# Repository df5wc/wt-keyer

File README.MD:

# Walkie-Talkie Keyer

So, hier isser: Der Walkie-Talkie Keyer. Das Projekt, an dem ich die letzten
Wochen nebenher rumgepusselt habe. Es ist eine komplette Hardware zum Betrieb
eines Handfunkgeräts als CW Station.

## Noch nie gestellte Fragen und ein paar Antworten:

### Was macht das Gerät?

CW über FM.

### Das kann ein Piepser, den ich ans Funkgerät halte. Wieso eine extra Hardware?

Der Walkie-Talkie Keyer übernimmt die komplette Steuerung. Er schaltet beim
ersten Zeichen das Handfunkgerät auf Sendung, generiert lokal einen Mithörton
und gibt die Morsezeichen auf das Funkgerät um wenige 100ms zeitverzögert aus.
Damit hat das Funkgerät Zeit, auf Sendung zu schalten. Mit dem Walkie-Talkie
Keyer ist CW mit einer Handfunke ähnlich komfortabel wie mit einem Gerät, das
CW native unterstützt: Einfach losmorsen. Das Gerät schaltet automatisch auf
Sendung und nach dem letzten Zeichen wieder zurück.

### Wofür braucht man das?

Ich habe es primär gebaut um auf dem Congress TOTA in CW machen zu können,
weil ich dort vermutlich nur ein Handfunkgerät haben werde. Der Walkie-Talkie
Keyer funktioniert aber nicht nur im Amateurfunk, sondern kann auch einfache
PMR Funkgeräte ansteuern und eignet sich deshalb auch zur Ausbildung oder als
Spaßprojekt für Kids. Der Keyer kann im Prinzip auch "große" Funkgeräte
ansteuern, solange diese PTT gegen Masse schalten und dafür keine hohen
Ströme/Spannungen notwendig sind.

### Gab's das nicht schon mal?

Ja, das gab's schon mal. Burkhard John (DK5JG) hat 2006 eine ähnliches Projekt
vorgestellt, den "FM-Keyer". Von diesem Gerät stammen einige der Ideen.
Schaltung, Software und Board des Walkie-Talkie Keyers sind aber komplett neu
und von mir.

### Paddle oder Handtaste?

Der Keyer kann beides, mit Handtaste ist aber keine Konfiguration möglich. Da
alle Einstellungen (bis auf "Handtaste oder Paddle") ausfallsicher gespeichert
werden, sollte das aber kein großes Problem sein. Nachdem die Konfiguration
mit einem Paddle durchgeführt wurde, kann mit genau diesen Einstellungen auch
eine Handtaste verwendet werden.

### Wie wird eine Handtaste erkannt?

Für ein Paddle wird ein 3,5 mm Stereo Klinkenstecker verwendet, für eine
Handtaste derselbe Stecker in Mono. Durch den Mono Stecker wird das rechte
Paddle ("Dah") an Masse gelegt. Das erkennt der Keyer beim Start und schaltet
direkt auf Handtaste um. Alternativ kann das rechte Paddle beim Start gedrückt
werden, oder mit dem "SK" Kommando (siehe unten) von Paddle auf Handtaste
umgeschaltet werden.

Die Einstellung "Handtaste" bleibt erhalten, bis der Keyer stromlos gemacht
wird. Ein Rückschalten durch Kommando ist nicht möglich.

### Wie bediene ich den Keyer?

Der Keyer benötigt externe 5V aus einem USB Port (Handy oder Power Bank). Er
wird auf der einen Seite mit dem Handfunkgerät verbunden. Auf der anderen
Seite wird die Taste angeschlossen. Neben der Einstellung für die Lautstärke
an der Seite gibt es an der Unterseite noch zwei Potis mit denen die Pegel für
das Handfunkgerät eingestellt werden können. Sie sollten bei der ersten
Inbetriebnahme auf jeweils 1/4 im Uhrzeigersinn eingestellt und dann nach
Gehör justiert werden. Bei Verwendung eines anderen Funkgeräts oder großen
Änderungen der Tonhöhe kann eine Nachjustierung notwendig sein.

Danach kann im Prinzip schon losgemorst werden. Zur Einstellung gibt es die
Taste &lt;Cmd&gt;. Wenn sie gedrückt und gehalten wird, können dem Keyer
Kommandos in CW gegeben werden. Hier ist die Liste der Kommandos:

* D?             query the tx delay
* Dnnn           set tx delay in ms
* IA             activate iambic A
* IB             activate iambic B
* IP             activate plain iambic mode
* M?1            query cw memory 1
* M?2            query cw memory 2
* M1...          program cw memory 1
* M2...          program cw memory 2
* O?             query tx off delay in dits
* Onn            set tx off delay in dits
* SK             switch to straight key
* SWD            disable paddle swap
* SWE            enable paddle swap
* T?             query the tone frequency
* TMD            disable training mode (TX)
* TME            enable training mode (no TX)
* Tnnn           set a tone frequency
* V?             query the software version number
* W?             query the keyer speed
* Wnn            set the keyer speed in wpm

Die Kommandos werden jeweils mit einem hohen Ton quittiert, wenn sie
erfolgreich ausgeführt wurden. Bei einem Fehler (oder einem unbekannten
Kommando) erfolgt eine Fehlerquittung (niedriger Ton).

Alle Einstellungen werden ausfallsicher gespeichert und stehen deshalb nach
dem nächsten Start genau so wieder zur Verfügung.

### Wie funktioniert das mit den CW Speichern?

Der Keyer verfügt über zwei Speicherplätze für Nachrichten in Morsecode. Diese
können über die Kommandos "M1" und "M2" programmiert und mit den Tasten
&lt;1&gt; und &lt;2&gt; abgerufen werden. Während ein Speichertext ausgegeben
wird, kann mittels Druck auf einen beliebigen Knopf oder Betätigung der
Morsetaste die Ausgabe abgebrochen werden.

Für die Programmierung wird &lt;Cmd&gt; gedrückt und "M1" oder "M2" mit dem
Paddle gegeben. Dann folgt der zu speichernde Text. Eine Pause von mindestens
2 Sekunden beendet die Eingabe mit einem Quittungston.

Um Speicherplatz zu sparen, werden alle Zeiten auf volle Vielfache der für ein
"Dit" benötigten Zeit gerundet. Der benötigte Speicherplatz pro Element mit
folgender Pause (also "Dit" oder "Dah") beträgt 1 Byte. Insgesamt stehen etwa
200 Bytes pro Speicherplatz zur Verfügung. Wird die maximale Länge eines
Speichers bei der Eingabe überschritten, erfolgt eine Fehlerquittung und der
Text wird nicht gespeichert. Die Programmierung kann auch durch Loslassen der
&lt;Cmd&gt; Taste vorzeitig abgebrochen werden (z.B. bei Fehltastung). Der
bereits gespeicherte Text bleibt dann erhalten.

### Wieso erfolgt die Tonausgabe des Handfunkgeräts über den Keyer?

Das ist bei Handfunkgeräten mit Kenwood "Norm" für den Anschluß eines externen
Mikrofons leider zwingend. Bei dieser Beschaltung werden zwei Stecker
verwendet, einer für Mikrofon/PTT, der andere für den Lautsprecher. Der
Stecker für Mikrofon/PTT führt aber keine Masse! Will man also PTT gegen Masse
schalten, muss zwingend auch der Lautsprecheranschluß verwendet werden. Dadurch
wird aber der interne Lautsprecher des Geräts abgeschaltet. Folglich muss die
Ausgabe über das angeschlossene Gerät erfolgen.

Wird eine andere Anschlußbeschaltung verwendet (von mir nicht getestet), dann
kann - falls das gewünscht ist - der "Speaker" Eingang am DIN Stecker des
Keyers einfach auf Masse gelegt, und der interne Lautsprecher des Geräts
verwendet werden. Der Mithörton kommt dann aus dem Lautsprecher des Keyers,
das Empfangssignal aus dem Lautsprecher des Funkgeräts.

### Welche Funkgeräte wurden getestet?

Ich habe den Keyer mit meinem Wouxun KG-UV6D und mit zwei verschiedenen PMR
Funkgeräten getestet. Alle diese Geräte hatten die Kenwood Anschlußbelegung.
Andere Anschlüsse sollten funktionieren, wenn PTT gegen Masse geschaltet wird
und keine hohen Ströme fliessen. Wenn keine Ausgabe des Empfangssignals über
die Keyer Hardware erfolgen soll, dann ist der entsprechende Eingang des
Keyers am DIN Stecker auf Masse zu legen.

### Ich habe ein Problem, wieso kann ich kein Issue anlegen?

Das Repository auf Github dient nur der Veröffentlichung, nicht der
Entwicklung. Für die Entwicklung wird ein anderes Repository verwendet.
Deshalb können auf Github keine Issues angelegt werden. Bei Problemen bitte
ich darum, mich per Mail zu kontaktieren.

### Gibt es bekannte Probleme?

Beim Prototyp hatte ich teilweise Probleme mit Einstrahlungen durch das
Handfunkgerät. Ich empfehle, ein abgeschirmtes Kabel für die Verbindung zum
Funkgerät zu verwenden und evtl. die Ferritperlen auf dem Board gegen kleine
Induktivitäten auszutauschen und/oder an der Stelle noch mit 100pF
abzublocken. Sobald mehr Erfahrungen vorliegen werde ich ggf. entsprechende
Änderungen der Schaltung vornehmen.

Die beiden Trimmer RV1 und RV2 werden von der Unterseite des Boards aus
bedient und haben deshalb die falsche Drehrichtung: Rechtsanschlag ist
Minimum, Linksanschlag ist Maximum.

### Ich kann mir das nicht vorstellen. Wie sieht der Keyer denn aus?

Hier sind Bilder vom aufgebauten Keyer und von einem kompletten Setup:

### Wo gibt's den Keyer zu kaufen?

Gar nicht (zumindest bei mir). Von mir gibt es

  - den Schaltplan,
  - einen PCB Entwurf,
  - die Software,
  - OpenSCAD Sourcen und STL Datei für das Gehäuse,
  - und eine minimale Doku

auf GitHub. Mit dabei ist eine Teileliste mit (größtenteils und ohne Garantie)
Reichelt Bestellnummern.

Wenn genug Interesse besteht, kann ich nochmals einen Satz Platinen fertigen
lassen und - solange übrig sind - welche abgeben. Ggf. mit programmierter AVR
CPU. Ich vertreibe aber keine Fertiggeräte oder Bausätze. Falls das jemand
machen will habe ich aber nichts dagegen.

### Ok, ich will bauen! Wie lege ich los?

Hier gibt es mehr Infos zum Aufbau:

* 
* 
* 

### Was gibt es sonst zu beachten?

Die Lizenz erlaubt so ziemlich alles, bis darauf die Entwürfe als eigene
auszugeben. Für Schäden beim Nachbau übernehme ich keine Haftung.

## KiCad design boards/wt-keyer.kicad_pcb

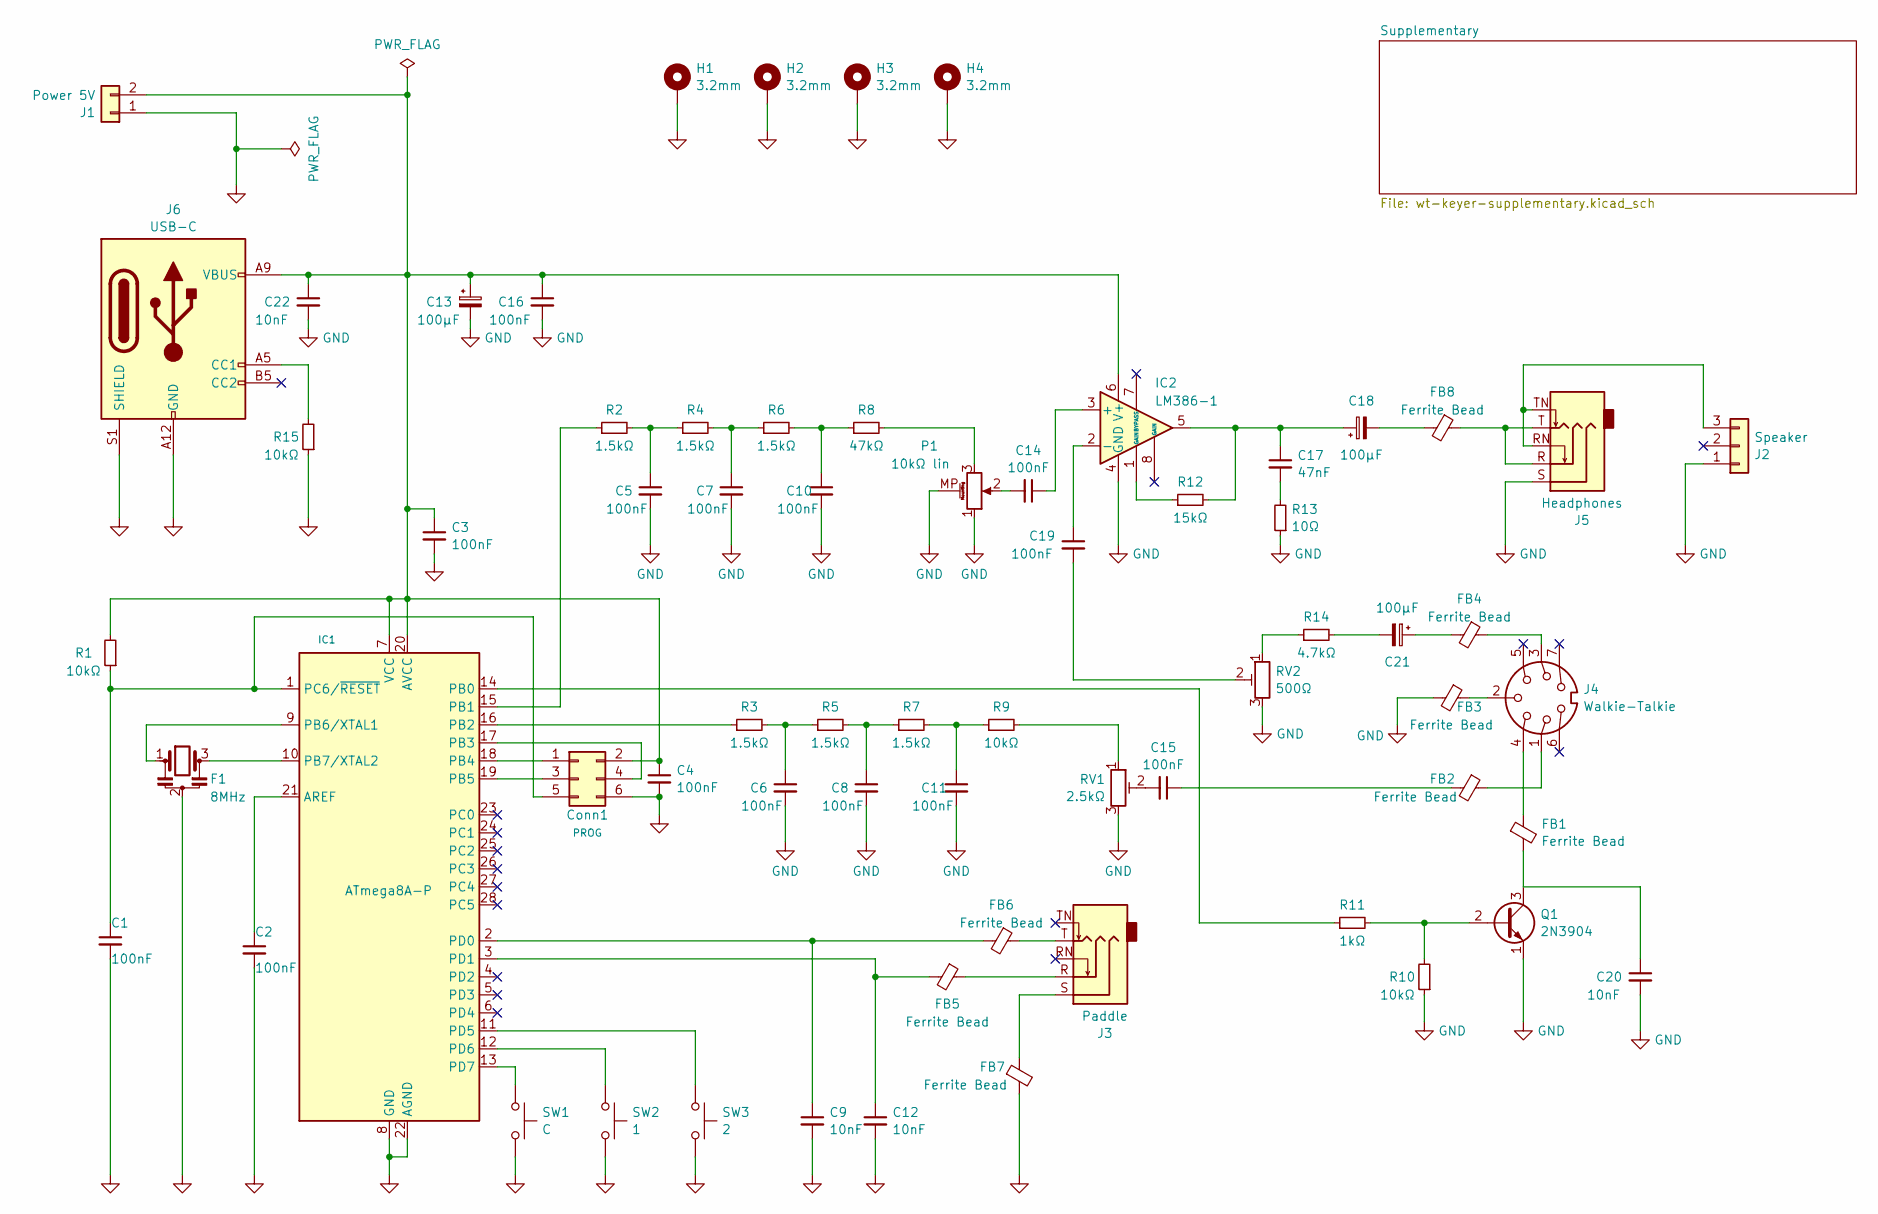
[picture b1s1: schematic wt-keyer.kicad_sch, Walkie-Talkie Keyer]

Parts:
C1, C2, C3, C4, C16: 100nF; C_Disc_D3.0mm_W1.6mm_P2.50mm
C5, C6, C7, C8, C10, C11, C14, C15, C19: 100nF; C_Rect_L4.6mm_W3.0mm_P2.50mm_MKS02_FKP02
C9, C12, C20, C22: 10nF; C_Disc_D3.0mm_W1.6mm_P2.50mm
C13, C18, C21: 100μF; CP_Radial_D5.0mm_P2.50mm
C17: 47nF; C_Rect_L4.6mm_W3.0mm_P2.50mm_MKS02_FKP02
Conn1: PROG; PinHeader_2x03_P2.54mm_Vertical
F1: 8MHz; Resonator-3Pin_W7.0mm_H2.5mm
FB1, FB2, FB3, FB4, FB5, FB6, FB7, FB8: Ferrite Bead; L_Axial_L9.5mm_D4.0mm_P2.54mm_Vertical_Fastron_SMCC
H1, H2, H3, H4: 3.2mm; MountingHole_3.2mm_M3_Pad_5.0mm_TopBottom
IC1: ATmega8A-P; DIP-28_W7.62mm
IC2: LM386-1; DIP-8_W7.62mm_Socket_LongPads
J1: Power 5V; FanPinHeader_1x02_P2.54mm_Vertical
J2: Speaker; FanPinHeader_1x03_P2.54mm_Vertical
J3: Paddle; Jack_3.5mm_Ledino_KB3SPRS_Horizontal
J4: Walkie-Talkie; DIN_7Pin_Horizontal
J5: Headphones; Jack_3.5mm_Ledino_KB3SPRS_Horizontal
J6: USB-C; USB_C_Receptacle_GCT_USB4125-xx-x-0190_6P_TopMnt_Horizontal
P1: 10kΩ lin; Potentiometer_Alps_RK09K_Single_Horizontal
Q1: 2N3904; TO-92_Inline
R1, R9, R10, R15: 10kΩ; R_Axial_DIN0207_L6.3mm_D2.5mm_P2.54mm_Vertical
R2, R3, R4, R5, R6, R7: 1.5kΩ; R_Axial_DIN0207_L6.3mm_D2.5mm_P2.54mm_Vertical
R8: 47kΩ; R_Axial_DIN0207_L6.3mm_D2.5mm_P2.54mm_Vertical
R11: 1kΩ; R_Axial_DIN0207_L6.3mm_D2.5mm_P2.54mm_Vertical
R12: 15kΩ; R_Axial_DIN0207_L6.3mm_D2.5mm_P2.54mm_Vertical
R13: 10Ω; R_Axial_DIN0207_L6.3mm_D2.5mm_P2.54mm_Vertical
R14: 4.7kΩ; R_Axial_DIN0207_L6.3mm_D2.5mm_P2.54mm_Vertical
RV1: 2.5kΩ; Potentiometer_Piher_PT-10-V10_Vertical
RV2: 500Ω; Potentiometer_Piher_PT-10-V10_Vertical
SW1: C; SW_PUSH_6mm_H4.3mm
SW2: 1; SW_PUSH_6mm_H4.3mm
SW3: 2; SW_PUSH_6mm_H4.3mm

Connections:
GND: C1.2, C2.2, C3.2, C4.2, C5.2, C6.2, C7.2, C8.2, C9.2, C10.2, C11.2, C12.2, C13.2, C16.2, C20.2, C22.2, Conn1.6, F1.2, FB3.2, FB7.2, H1.1, H2.1, H3.1, H4.1, IC1.8 (GND), IC1.22 (AGND), IC2.4 (GND), J1.1, J2.1, J5.S, J6.A12 (GND), J6.B12 (GND), J6.S1 (SHIELD), P1.1, P1.MP (MountPin), Q1.1 (E), R10.1, R13.1, R15.1, RV1.3, RV2.3, SW1.2, SW2.2, SW3.2
unnamed: C5.1, R2.2, R4.1
unnamed: C6.1, R3.2, R5.1
unnamed: C7.1, R4.2, R6.1
unnamed: C8.1, R5.2, R7.1
unnamed: C10.1, R6.2, R8.1
unnamed: C11.1, R7.2, R9.1
unnamed: C14.2, P1.2
unnamed: C15.1, FB2.2
unnamed: C15.2, RV1.2
unnamed: C17.1, C18.1, IC2.5, R12.2
unnamed: C17.2, R13.2
unnamed: C18.2, FB8.2
unnamed: C19.2, RV2.2
unnamed: C21.1, FB4.2
unnamed: C21.2, R14.2
unnamed: Conn1.1, IC1.18 (PB4)
unnamed: C3.1, C4.1, C13.1, C16.1, C22.1, Conn1.2, IC1.7 (VCC), IC1.20 (AVCC), IC2.6 (V+), J1.2, J6.A9 (VBUS), J6.B9 (VBUS), R1.2
unnamed: Conn1.3, IC1.19 (PB5)
unnamed: Conn1.4, IC1.17 (PB3)
unnamed: C1.1, Conn1.5, IC1.1 (PC6/~RESET), R1.1
unnamed: FB1.1, J4.4
unnamed: FB2.1, J4.1
unnamed: FB3.1, J4.2
unnamed: FB4.1, J4.3
unnamed: FB5.1, J3.R
unnamed: FB6.1, J3.T
unnamed: FB7.1, J3.S
unnamed: FB8.1, J5.R, J5.T
unnamed: C2.1, IC1.21 (AREF)
unnamed: IC1.14 (PB0), R11.1
unnamed: IC1.15 (PB1), R2.1
unnamed: IC1.16 (PB2), R3.1
unnamed: F1.1, IC1.9 (PB6/XTAL1)
unnamed: F1.3, IC1.10 (PB7/XTAL2)
unnamed: C9.1, FB6.2, IC1.2 (PD0)
unnamed: C12.1, FB5.2, IC1.3 (PD1)
unnamed: IC1.11 (PD5), SW3.1
unnamed: IC1.12 (PD6), SW2.1
unnamed: IC1.13 (PD7), SW1.1
unnamed: C14.1, IC2.3 (+)
unnamed: C19.1, IC2.2 (-)
unnamed: IC2.1 (GAIN), R12.1
unnamed: J2.3, J5.RN, J5.TN
unnamed: J6.A5 (CC1), R15.2
unnamed: P1.3, R8.2
unnamed: Q1.2 (B), R10.2, R11.2
unnamed: C20.1, FB1.2, Q1.3 (C)
unnamed: R9.2, RV1.1
unnamed: R14.1, RV2.1

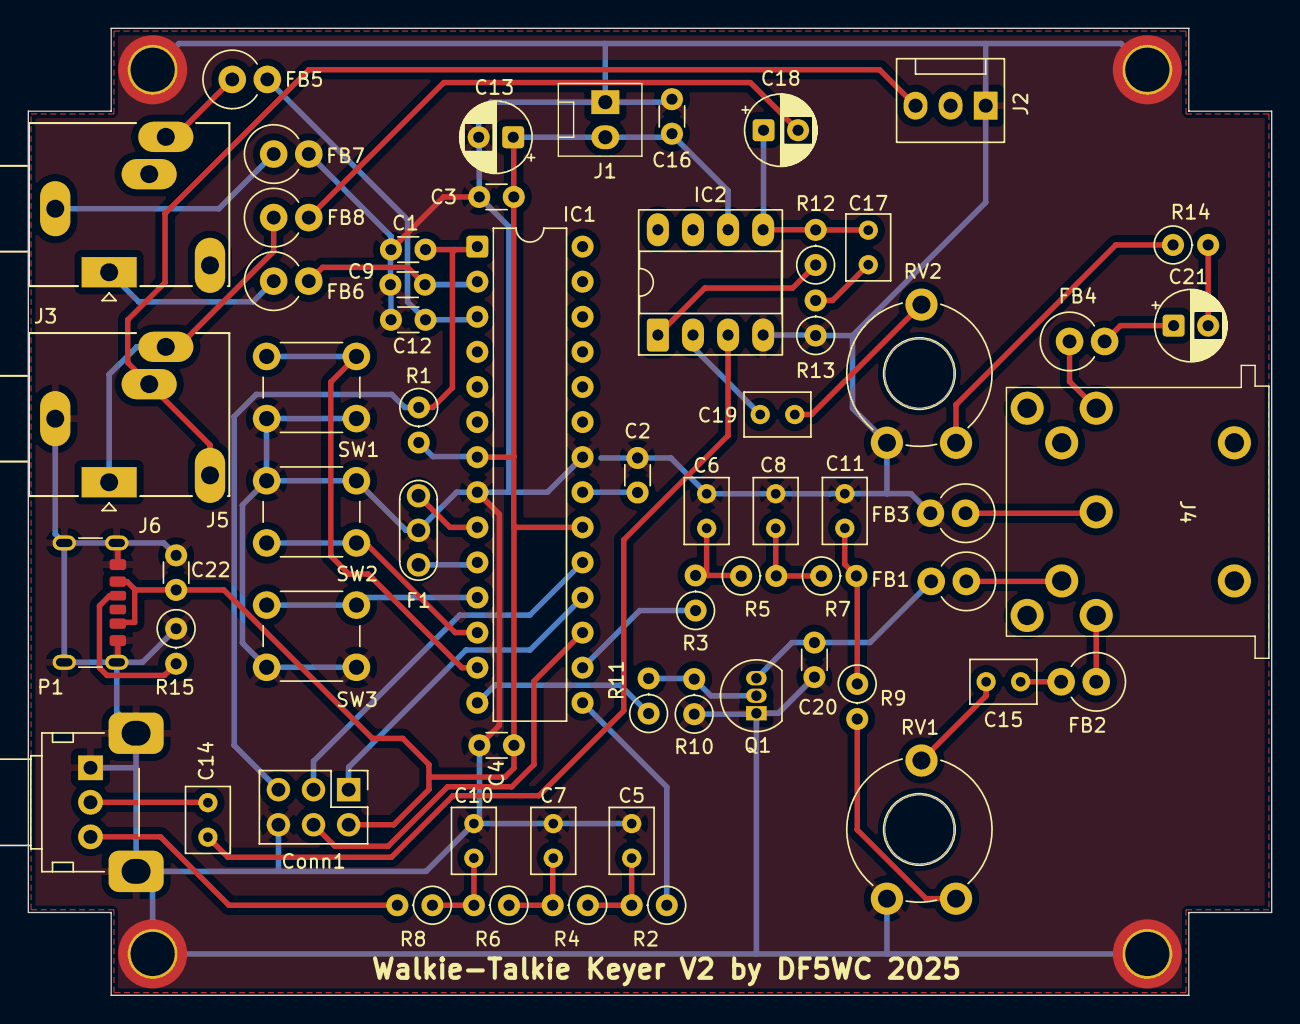
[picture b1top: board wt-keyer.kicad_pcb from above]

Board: 2 copper layers, 90.0 x 70.0 mm, 66 parts (0 on the bottom side), 50 nets.

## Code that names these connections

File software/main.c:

/*****************************************************************************/
/*                                                                           */
/*                                  main.c                                   */
/*                                                                           */
/*                     Dual tone generator main program                      */
/*                                                                           */
/*                                                                           */
/*                                                                           */
/* (C) 2025,      Ullrich von Bassewitz                                      */
/*                Roemerstrasse 52                                           */
/*                D-70794 Filderstadt                                        */
/* EMail:         uz@df5wc.org                                               */
/*                                                                           */
/*                                                                           */
/* This software is provided 'as-is', without any expressed or implied       */
/* warranty.  In no event will the authors be held liable for any damages    */
/* arising from the use of this software.                                    */
/*                                                                           */
/* Permission is granted to anyone to use this software for any purpose,     */
/* including commercial applications, and to alter it and redistribute it    */
/* freely, subject to the following restrictions:                            */
/*                                                                           */
/* 1. The origin of this software must not be misrepresented; you must not   */
/*    claim that you wrote the original software. If you use this software   */
/*    in a product, an acknowledgment in the product documentation would be  */
/*    appreciated but is not required.                                       */
/* 2. Altered source versions must be plainly marked as such, and must not   */
/*    be misrepresented as being the original software.                      */
/* 3. This notice may not be removed or altered from any source              */
/*    distribution.                                                          */
/*                                                                           */
/*****************************************************************************/



#include <stdbool.h>
#include <stdint.h>
#include <avr/io.h>
#include <avr/sleep.h>

/* wt-keyer */
#include "buttons.h"
#include "config.h"
#include "cw.h"
#include "cwmem.h"
#include "keyer.h"
#include "rigctrl.h"
#include "timer.h"
#include "tone.h"
#include "version.h"



/*****************************************************************************/
/*                             Helper functions                              */
/*****************************************************************************/



static void SetupIO(void)
/* Setup I/O stuff */
{
    /* IO Ports: PB0 and PB1/PB2 (= OC1A/OC1B) are outputs */
    DDRB = 0x07;

    /* Port C is currently unused and configured as input */
    DDRC = 0x00;
    PORTC = 0x00;       /* Tri-state port C */

    /* Port D is an input. Used bits are PD0/PD1/PD5/PD6/PD7 */
    DDRD = 0x00;
    PORTD = 0xE3;       /* Activate pullups for all used port bits */

    /* Setup tone generation */
    SetupTone();

    /* Setup the timer ticker */
    SetupTimer();
}



/*****************************************************************************/
/*                               Main program                                */
/*****************************************************************************/



int main(void)
{
    /* Initialize I/O and modules */
    SetupIO();
    SetupCw();
    SetupCwMem();
    SetupKeyer();
    SetupRigCtrl();

    /* Run forever */
    while (1) {
        /* Run the keyer. If it is idle, handle switches. React only on button
         * press, not release.
         */
        Keyer();
        uint8_t B;
        if ((B = (ChangedButtons & Buttons)) != BUTTON_NONE) {
            /* Keyer is idle. Force TX and memory play off, then handle
             * switches.
             */
            TxAbort();
            switch (B) {
                case BUTTON_C:
                    AbortPlayCwMem();
                    Configuration();
                    break;

                case BUTTON_1:
                    if (CwMemIsPlaying()) {
                        AbortPlayCwMem();
                    } else {
                        StartPlayCwMem(CWMEM_1);
                    }
                    break;

                case BUTTON_2:
                    if (CwMemIsPlaying()) {
                        AbortPlayCwMem();
                    } else {
                        StartPlayCwMem(CWMEM_2);
                    }
                    break;

                default:
                    /* Ignore other button combinations */
                    break;
            }
            /* Reinitialize keyer and buffer */
            ResetKeyer();
        } else {
            /* Play cw memories if active */
            if (CwMemIsPlaying()) {
                /* Allow aborting with the paddle or straight key. Beware: If
                 * a straight key is used, dah may be tied to ground.
                 */
                if (Dit(Keys) || (!StraightKey && Dah(Keys))) {
                    AbortPlayCwMem();
                } else {
                    PlayCwMem();
                }
            }

            /* Send elements read by the keyer */
            TxSend();
        }

        /* Clear changed buttons and wait for the next timer interrupt */
        ChangedButtons = 0;
        sleep_cpu();
    }
}

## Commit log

2025-10-12 Added the license file
2025-10-12 Added the current state of the project.
2025-10-12 A few additions to the readme.
2025-10-12 Added the schematics as PDF.
2025-10-12 Added a note about problems with the boards under "known problems".
2025-10-17 Added some pictures.
2025-10-22 Remove the paragraph that talks about a hissing sound. It comes from the 5V power supply, not the keyer itself.
2025-10-31 Updated the files for V2 of the walkie-talkie keyer.
2025-10-31 Fixed document links.
2025-10-31 The [!...] markup items need special syntax.
2025-10-31 Adjusted the levels of some key paragraphs.
2025-10-31 Added a PDF version of the parts list.
2025-10-31 Small fixes.
2025-11-01 Use the ATMega8L for less current consumption.
2025-11-02 Added an additional "Alternative" column to the parts list.
